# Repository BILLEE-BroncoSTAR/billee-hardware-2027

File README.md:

# BILLEE Hardware 2027
### By Luca Lanzillotta

This repository contains the hardware design and simulation files for the BILLEE Rover Control Module, schematic diagrams for the Science Control Module, F´/Zephyr firmware, Science Arduino firmware, and all supporting resources required to operate BILLEE for URC 2027.
If you are looking for our ROS2 Humble Software Stack, refer to [billee-software-2027](https://github.com/BroncoSpace-BILLEE/URC-2027).

## Table of contents

- [Rover architecture](#rover-architecture)
- [Repository layout](#repository-layout)
- [System architecture](#system-architecture)
- [BILLEE Rover Control Module PCB](#billee-rover-control-module-pcb)
  - [System overview](#system-overview)
  - [Power architecture](#power-architecture)
  - [Per-channel protection chain](#per-channel-protection-chain)
  - [Subsystems](#subsystems)
  - [Connectors](#connectors)
  - [RCM Firmware](#rcm-firmware)
- [BILLEE Science Control Module Schematic](#billee-science-control-module-schematic)
  - [SCM Firmware](#scm-firmware)
- [BILLEE Drivetrain Module Schematic](#billee-drivetrain-module-schematic)
- [BILLEE Arm Module Schematic](#billee-arm-module-schematic)
- [BILLEE Astronaut Module Schematic](#billee-astronaut-module-schematic)
- [Drivetrain motor calibration — ODESC Configuration](#drivetrain-motor-calibration--odesc-configuration)
- [Science spectrometer tooling](#science-spectrometer-tooling)
- [Astronaut video/audio streamer](#astronaut-videoaudio-streamer)
- [UV science camera](#uv-science-camera)
- [Getting started](#getting-started)
- [Design status](#design-status)
- [Contributors](#contributors)

## Rover architecture

A full-system view of BILLEE, from the operator at the ground station down to
each subsystem on the rover. Every link from the ground station to the rover
goes over the Ubiquiti Prism point-to-point link to the Jetson. The Jetson
then reaches the RCM and SCM over F´, the drivetrain over CAN, the arm over
GPIO, and the science instruments and astronaut module over USB, Bluetooth LE
and Wi-Fi. Thick arrows are power from the RCM, normal arrows are data, and the
dashed arrow is ROS2 control from the ground station.

```mermaid
flowchart TB
    %% ================= GROUND STATION =================
    OP(["Ground Station: Operator<br/>ROS2 control · F´ GDS · science + video dashboards"])

    %% ================= COMMS =================
    UBG["Ground Station Comms Link<br/>Ubiquiti Prism"]
    UBR["Rover Comms Link<br/>Ubiquiti Prism"]

    OP --> UBG
    UBG <-->|"point-to-point wireless link"| UBR

    %% ================= ROVER =================
    subgraph ROVER["BILLEE Rover"]
        direction TB

        JETSON["Jetson Orin AGX<br/>Main Compute · ROS2"]
        ZED["ZED 2 Camera"]
        RCM["Rover Control Module<br/>RP2350 · power distribution"]
        DRV["Drivetrain<br/>6× ODESC + NEO motors"]
        ARM["Arm Module<br/>3-axis arm + end effector"]

        subgraph SCI["Science"]
            direction TB
            SCM["Science Control Module<br/>Teensy 4.1"]
            SPEC["Spectroscopy<br/>Vernier spectrometer"]
            UV["UV Spectroscopy<br/>+ UV camera"]
            DRILL["Drill<br/>Regolith Extraction"]
            CHEM["Chemical Management<br/>pumps"]
            CACHE["Sample Cache<br/>+ Rotation"]
            SCM --> DRILL
            SCM --> CHEM
            SCM --> CACHE
            SCM --> UV
        end

        UBR -- "Ethernet" --> JETSON
        ZED -- "USB" --> JETSON
        JETSON <-->|"F´"| RCM
        JETSON <-->|"F´"| SCM
        JETSON -- "Bluetooth" --> SPEC
        JETSON -- "USB" --> UV
        JETSON -- "CAN" --> DRV
        JETSON -- "commands" --> ARM

        RCM == "power" ==> JETSON
        RCM == "power" ==> DRV
        RCM == "power" ==> ARM
        RCM == "power" ==> SCM
    end

    ASTRO["Astronaut Module<br/>Raspberry Pi 4B · camera + headset"]
    ASTRO -- "Wi-Fi video + audio" --> JETSON

    %% ================= ROS2 CONTROL =================
    OP -. "ROS2 control" .-> JETSON

    %% ================= STYLES =================
    classDef ground fill:#1f4e79,stroke:#0d2a45,color:#fff
    classDef comms fill:#7b3fa0,stroke:#4a2063,color:#fff
    classDef compute fill:#2e7d32,stroke:#1b4d1f,color:#fff
    classDef rcm fill:#c62828,stroke:#7f1414,color:#fff
    classDef science fill:#ef6c00,stroke:#8a3e00,color:#fff
    classDef motion fill:#455a64,stroke:#263238,color:#fff
    classDef astro fill:#00838f,stroke:#004f56,color:#fff

    class OP ground
    class UBG,UBR comms
    class JETSON,ZED compute
    class RCM rcm
    class SCM,SPEC,UV,DRILL,CHEM,CACHE science
    class DRV,ARM motion
    class ASTRO astro
```

The [System architecture](#system-architecture) section below zooms in on
the boards in this repo and how they connect.

## Repository layout

```
billee-hardware-2027/
├── BILLEE_Arm_Module/                    # KiCad project for the Arm Schematic
├── BILLEE_Astronaut_Module/              # KiCad project for the Astronaut Module Schematic
│   └── AstronautModuleAssembly/          # SolidWorks assembly: Raspberry Pi 4 mount + lid, Pi 4 datasheet
├── BILLEE_Drivetrain_Module/             # KiCad schematic documenting the drivetrain wiring (ODESC + NEO + CAN)
├── BILLEE_Rover_Control_Module_V1/       # KiCad project for the Rover Control Module
├── BILLEE_Science_Control_Module_V1/     # KiCad project for the Science Control Module
├── BILLEE-odesc-config-tool/             # Python tool: USB ODESC motor calibration
├── RunScienceSpectrometer/               # Offline Vernier spectrometer PWA + kiosk setup for the Jetson
├── astronaut-streamer/                   # Pi camera → Jetson → ground-station video + audio stream (git submodule)
├── fprime-billee-rcm/                    # F´ firmware for the RCM board (git submodule)
├── fprime-arduino-billee-scm/            # F´ firmware for the Science Control Module (git submodule)
├── uv_scienceCam/                        # USB Arducam → browser stream with live image tuning + snapshots (git submodule)
└── Makefile                              # Workspace bootstrap (`make setup`/`make rover`) + science/astronaut installers
```

## System architecture

BILLEE's compute and control hardware breaks down into a Jetson Orin AGX main
compute module, the Rover Control Module (RCM, this repo's primary board),
the Science Control Module (SCM), and the drivetrain's ODESC motor
controllers. The RCM both powers the Jetson and exchanges F´ telemetry/
commands with it; the SCM and the Jetson each run their own F´ deployment,
talking over separate USB connections and separate GDS dashboard ports so
both can be open at once.

```mermaid
flowchart TB
    Jetson["Jetson Orin AGX<br/>Main compute<br/>(ROS2 stack — billee-software-2027)"]

    subgraph RCM["Rover Control Module — BILLEE_Rover_Control_Module_V1 (KiCad)"]
        RCM_FW["RP2350<br/>fprime-billee-rcm (F´ / Zephyr)"]
    end

    subgraph SCM["Science Control Module — BILLEE_Science_Control_Module_V1 (KiCad)"]
        SCM_FW["Teensy 4.1<br/>fprime-arduino-billee-scm (F´)"]
    end

    RCM_FW -- "+20V power (CN2)" --> Jetson
    Jetson -- "USB CDC / F´ GDS :5000" --> RCM_FW
    Jetson -- "USB CDC / F´ GDS :5001" --> SCM_FW
    Jetson -- "Bluetooth LE" --> SPEC["Vernier Go Direct spectrometer<br/>(RunScienceSpectrometer)"]

    subgraph DRV["Drivetrain Module — BILLEE_Drivetrain_Module (KiCad)"]
        ODESC["6x ODESC V4.2 + NEO motors"]
    end

    RCM_FW -- "6x switched DRIVE outputs" --> ODESC
    Jetson -- "USB CANable / CAN bus" --> ODESC
    subgraph ARMM["Arm Module — BILLEE_Arm_Module (KiCad)"]
        ARM["3-axis arm actuators<br/>+ end-effector solenoid"]
    end

    RCM_FW -- "switched ARM output" --> ARM
    Jetson -- "GPIO27 → solenoid relay" --> ARM
    RCM_FW -- "switched SCIENCE output" --> SCM_FW

    ODESC -. "USB, one-time calibration" .-> TOOL["BILLEE-odesc-config-tool<br/>(odrive Python tool)"]
```

Solid arrows are runtime power/data paths; the dashed arrow is the ODESC
calibration tool's occasional USB connection, not part of the running
topology. Runtime drivetrain/arm motor commands come from the ROS2 stack in
[billee-software-2027](https://github.com/BroncoSpace-BILLEE/URC-2027), outside
this repo's scope — the RCM only switches and protects their power.

### Hardware ↔ Firmware

| Hardware (KiCad project) | Firmware | Target | Role |
|---|---|---|---|
| [`BILLEE_Rover_Control_Module_V1/`](BILLEE_Rover_Control_Module_V1/) | [`fprime-billee-rcm`](fprime-billee-rcm/README.md) | RP2350 (F´ / Zephyr) | Power distribution/gating for DRIVE, ARM, and SCIENCE; powers the Jetson; reports subsystem/E-Stop/thermal telemetry over USB |
| [`BILLEE_Science_Control_Module_V1/`](BILLEE_Science_Control_Module_V1/) — | [`fprime-arduino-billee-scm`](fprime-arduino-billee-scm/README.md) | Teensy 4.1 (F´) | Science instrument control, USB CDC to Jetson |
| [`BILLEE_Arm_Module/`](BILLEE_Arm_Module/) — arm wiring (off-the-shelf actuators, documented here) | — | — | Arm axis actuators and end-effector solenoid, powered from the RCM's switched ARM output |
| [`BILLEE_Drivetrain_Module/`](BILLEE_Drivetrain_Module/) — ODESC motor controllers (third-party hardware, wiring documented here) | [`BILLEE-odesc-config-tool`](BILLEE-odesc-config-tool/README.md) | ODrive-based ODESC | One-time/occasional USB calibration tool (encoder/motor cal, CAN node ID) — not runtime firmware |

BILLEE is a Mars-rover-style rover platform built as a university project. This repository holds the hardware for the **Rover Control Module (RCM)** — the rover's central power distribution and control board. It takes in power from up to four independent battery packs, gates and protects eight switched high-current outputs (six drivetrain channels plus dedicated ARM and SCIENCE subsystem outputs), and hosts the RP2350 microcontroller that supervises the whole board, running [NASA JPL's F´ (F Prime)](https://fprime.jpl.nasa.gov/) flight software framework on Zephyr RTOS.

## BILLEE Rover Control Module PCB

## System overview

```mermaid
flowchart TB
    subgraph Power["Power inputs (4 independent battery packs)"]
        LOGIC_BATT["LOGIC BATT<br/>22.2V / 6S<br/>CN1"]
        DRIVE_BATT["DRIVE BATT<br/>14.4V / 4S<br/>CN7"]
        ARM_BATT["ARM BATT<br/>22.2V / 6S<br/>CN9"]
        SCI_BATT["SCIENCE BATT<br/>22.2V / 6S<br/>CN8"]
    end

    subgraph Control["Control plane"]
        RP2350["RP2350<br/>Fprime-zephyr"]
        ESTOP["E-Stop circuit"]
        FLASH["W25Q128 flash"]
        TEMP["MCP9808 temp sensors"]
        RP2350 --- FLASH
        RP2350 --- TEMP
        ESTOP -- "cuts ARM / SCIENCE / DRIVE enables" --> RP2350
    end

    subgraph Outputs["Switched, gated, current-sensed outputs"]
        DRIVE_OUT["6x DRIVE channels<br/>XT60, CN10-CN15"]
        ARM_OUT["ARM output<br/>XT60 x2, CN17/CN18"]
        SCI_OUT["SCIENCE output<br/>XT60, CN16"]
    end

    subgraph Aux["Auxiliary rails"]
        LOGIC3V3["+3.3V RP2350 / logic"]
        LOGIC12V["+12V AUX (gate driver bias)"]
        POE["+22.2V POE out<br/>XT60, CN3"]
        JETSON["+20V Jetson out<br/>XT60, CN2"]
    end

    LOGIC_BATT --> Reg["Onboard regulation<br/>(buck converters + e-fuses)"]
    Reg --> LOGIC3V3
    Reg --> LOGIC12V
    Reg --> POE
    Reg --> JETSON
    Reg -. powers control plane .-> RP2350

    DRIVE_BATT --> DRIVE_OUT
    ARM_BATT --> ARM_OUT
    SCI_BATT --> SCI_OUT

    RP2350 -- "GPIO enable per channel" --> DRIVE_OUT
    RP2350 -- "GPIO enable" --> ARM_OUT
    RP2350 -- "GPIO enable" --> SCI_OUT
```

## Power architecture

Every high-current output is switched, not just fused — each channel has its own MOSFET high-side switch, gate driver, and current/voltage sense IC, controlled by the RP2350 and independently protected against overvoltage.

| Input | Voltage | Pack | Connector | Feeds |
|---|---|---|---|---|
| LOGIC | 22.2V nominal | 6S | CN1 (XT90) | Onboard regulation → 3.3V logic, 12V gate-driver bias, POE out, Jetson out |
| DRIVE | 14.4V nominal | 4S | CN7 (XT90) | 6x independently gated drivetrain outputs |
| ARM | 22.2V nominal | 6S | CN9 (XT90) | ARM actuator output (dedicated, not shared with LOGIC) |
| SCIENCE | 22.2V nominal | 6S | CN8 (XT90) | SCIENCE payload output (dedicated, not shared with LOGIC) |

ARM and SCIENCE each have their own battery input rather than sharing the LOGIC bus — this keeps their (higher-current, motor-driven) load switching electrically isolated from the board's own logic supply.

## Per-channel protection chain

The same signal chain protects all eight switched outputs (six DRIVE channels, ARM, SCIENCE) — this is what sits between the RP2350's enable GPIO and the actual output connector:

```mermaid
flowchart LR
    GPIO["RP2350 GPIO<br/>(per-channel enable)"] --> BUF["Logic buffer<br/>(SN74LVC08A AND gate)"]
    ESTOP["E-Stop status"] --> BUF
    BUF --> DRV["LTC7001<br/>gate driver"]
    OVLO["OVLO divider<br/>(866k/34k → 1.21V trip)"] --> DRV
    DRV --> FET["IPT007N06N<br/>high-side MOSFET<br/>(60V rated)"]
    FET --> ISENSE["INA780x<br/>current + voltage sense<br/>(85V CMV)"]
    ISENSE --> OUT["Output connector"]
```

Each channel's overvoltage lockout trips at roughly the same ~32V threshold regardless of that channel's nominal rail — set by a fixed 866kΩ/34kΩ divider into the gate driver's 1.21V comparator reference. The MOSFETs and current-sense amplifiers were selected with wide margin above every rail on this board (60V and 85V ratings against a top end around 25V), so the same switch/sense stage is reused across the 14.4V DRIVE channels and the 22.2V ARM/SCIENCE channels without modification.

## Subsystems

| Subsystem | Sheet | What's there |
|---|---|---|
| RP2350A | `mcurp2350.kicad_sch` | RP2350 MCU, crystal, QSPI flash, USB-C, SWD debug header, GPIO breakout |
| Logic Subsystem | `power.kicad_sch` | Buck regulators, e-fuses, logic/auxiliary rail generation |
| Subsystem Power Control | `estop.kicad_sch` | E-stop circuit, all 8 gate-driver/switch/sense channels, OVLO dividers |

## Connectors

| Ref | Part | Count | Purpose |
|---|---|---|---|
| CN1 | XT90PW | 1 | LOGIC battery input (22.2V) |
| CN7 | XT90PW | 1 | DRIVE battery input (14.4V) |
| CN8 | XT90PW | 1 | SCIENCE battery input (22.2V) |
| CN9 | XT90PW | 1 | ARM battery input (22.2V) |
| CN10–CN15 | XT60PW | 6 | DRIVE channel outputs 1–6 |
| CN16 | XT60PW | 1 | SCIENCE output |
| CN17, CN18 | XT60PW | 2 | ARM output |
| CN2 | XT60PW | 1 | Jetson power output (+20V) |
| CN3 | XT60PW | 1 | POE output (+22.2V) |
| CN4, CN5 | XT60PW | 2 | Auxiliary +12V outputs |
| CN6 | DF11-18DP | 1 | RP2350 GPIO breakout (9 GPIO + ADC0/1 + power/GND) |
| USB1 | USB-C | 1 | RP2350 USB |
| J1 | 2.54mm header | 1 | SWD debug (SWCLK/SWD/GND) |

## RCM Firmware

The RCM's RP2350 runs [F´](https://fprime.jpl.nasa.gov/) on Zephyr RTOS —
subsystem power enable/disable, E-Stop handling, and MCP9808/INA780B thermal
and power telemetry, communicating with the Jetson over USB CDC. To get
started:

```bash
cd fprime-billee-rcm
make setup      # creates fprime-venv, inits submodules, installs requirements.txt
```

See [`fprime-billee-rcm/README.md`](fprime-billee-rcm/README.md) for the rest
(`make setup-zephyr`, `make build-rp2350`, flashing, GDS), and
[`docs/OPERATOR_MANUAL.md`](fprime-billee-rcm/docs/OPERATOR_MANUAL.md) for the
command/telemetry reference.

## BILLEE Science Control Module Schematic

[`BILLEE_Science_Control_Module_V1/`](BILLEE_Science_Control_Module_V1/)
is an early-stage KiCad project; this section will be filled in with the
schematic and hardware documentation once the module design is integrated.

## SCM Firmware

The SCM runs F´ on a Teensy 4.1, communicating with the Jetson over its own
USB CDC connection (GDS on port 5001, alongside the RCM's on port 5000). To
get started:

```bash
cd fprime-arduino-billee-scm
make setup      # creates fprime-venv, inits submodules, installs Python deps
```

See [`fprime-arduino-billee-scm/README.md`](fprime-arduino-billee-scm/README.md)
for the rest (`make setup-arduino`, `make generate`, `make build`, flashing).

## BILLEE Drivetrain Module Schematic

[`BILLEE_Drivetrain_Module/`](BILLEE_Drivetrain_Module/) is a KiCad
schematic documenting the drivetrain wiring as built for the '24 URC season:
six ODESC V4.2 controllers, each driving a NEO brushless motor with Hall
feedback, fed from the RCM's six switched `DRIVE` outputs and sharing a CAN
bus that reaches the Jetson through a USB CANable. It's wiring documentation
for the third-party hardware, not a custom PCB.

## BILLEE Arm Module Schematic

[`BILLEE_Arm_Module/`](BILLEE_Arm_Module/) is a KiCad schematic documenting
the 2027 robotic arm's wiring: P17/P20 harmonic-reducer actuators on the 1st,
2nd and 3rd axes, Yellow Jacket motors, and a GX20 14-pin bulkhead connector
between the rover body and the arm. The end effector carries a typing
solenoid, switched by a logic-level relay driven from Jetson GPIO27
(header pin 15). Power comes from the RCM's `+22.2V_ARM` output through a
front-panel Anderson Powerpole. Electronics by Luca Lanzillotta and Jason
Lau; mechanical design by Justin Chang.

## BILLEE Astronaut Module Schematic

[`BILLEE_Astronaut_Module/`](BILLEE_Astronaut_Module/) is a KiCad
block-diagram schematic of the astronaut module's hardware: a Raspberry Pi 4B
powered over USB-C to USB-C from an Anker Prime 27,650 mAh power bank, with
wired headphones on a 3.5 mm jack (no mic). This is the Pi that runs the
sender side of the [astronaut video/audio streamer](#astronaut-videoaudio-streamer).
Like the drivetrain schematic, it documents off-the-shelf hardware and is not
a custom PCB.

[`AstronautModuleAssembly/`](BILLEE_Astronaut_Module/AstronautModuleAssembly/)
holds the SolidWorks models for the module's enclosure:
`AstronautModuleAssembly.SLDASM`, the `PiMount` and `PiMountLid` parts, and
the Raspberry Pi 4 datasheet for reference.

## Drivetrain motor calibration — ODESC Configuration

[`BILLEE-odesc-config-tool`](BILLEE-odesc-config-tool/README.md) is a
Python tool (not firmware) for calibrating an ODESC-controlled drivetrain
motor over USB — encoder/motor calibration, CAN node ID setup, and saving
config to flash. It's a one-time/occasional setup step per motor, separate
from runtime motor control.

## Science spectrometer tooling

[`RunScienceSpectrometer`](RunScienceSpectrometer/README.md) sets up an
offline-capable copy of Vernier's Spectral Analysis PWA on the Jetson, talking
to a Go Direct spectrometer over Bluetooth LE, with an optional headless
VNC kiosk mode.

## Astronaut video/audio streamer

[`astronaut-streamer`](https://github.com/LucaLanzi/astronaut-streamer) (git
submodule) streams live video and audio from a USB camera on a Raspberry Pi 4B
to the Jetson over the Jetson's Wi-Fi hotspot. The Jetson forwards it to a
browser at the ground station over the Ubiquiti Prism link, at
`https://10.110.0.230:8443`, and the ground station can talk back to the
astronaut's headphones. Everything installs from this repo's root:

```bash
make astronaut jetson   # on the Jetson: packages, media server, dashboard, services, hotspot
make astronaut pi       # on the Pi: packages, Wi-Fi, SSH, sender service
make astronaut probe    # on the Pi: bench check (camera, mic, speaker, encoders, Wi-Fi)
make astronaut status   # on either: what's running
make astronaut jetson ip rover 192.168.4.97/22   # other addresses (defaults: the rover's)
make astronaut          # every command (logs, restart, test-pattern, view, test, e2e, ...)
```

Step by step: [`astronaut-streamer/docs/RUN_GUIDE.md`](astronaut-streamer/docs/RUN_GUIDE.md).
Full reference: [`astronaut-streamer/docs/SETUP.md`](astronaut-streamer/docs/SETUP.md).
Hardware test plan:
[`astronaut-streamer/docs/TEST_CHECKLIST.md`](astronaut-streamer/docs/TEST_CHECKLIST.md).
Design: [`astronaut-streamer/PLAN.md`](astronaut-streamer/PLAN.md).

## UV science camera

[`uv_scienceCam`](https://github.com/LucaLanzi/uv_scienceCam) (git
submodule) streams a USB (UVC) Arducam to a browser over the network. From
the browser you can tune the camera's image controls live (exposure, gain,
white balance, etc.), save/load tuning profiles as JSON, and take a
full-resolution picture that downloads to the viewing computer. It serves on
port 8090 to stay clear of the ports already in use on the Jetson. On the
machine the camera is plugged into:

```bash
cd uv_scienceCam
make setup      # apt packages, .venv, video group, firewall port
make list       # find the camera
make run        # camera 0, largest MJPG size, port 8090
```

Then open `http://<camera-host-ip>:8090/`. See
[`uv_scienceCam/README.md`](uv_scienceCam/README.md) for options and the HTTP
API.

## Getting started

1. Clone with submodules — the F´ component library is a separate repo:
   ```
   git clone --recurse-submodules https://github.com/BroncoSpace-BILLEE/billee-hardware-2027.git
   ```
   Already cloned, or need to resync after a branch change? Run `make rover` from
   the repo root — it checks out `lucadev`, pulls, and updates every submodule
   recursively. `make help` lists all targets.
2. Open `BILLEE_Rover_Control_Module_V1/BILLEE_Rover_Control_Module_V1.kicad_pro` in KiCad. The custom library footprints under `lib/` are wired up via the project's `fp-lib-table`/`sym-lib-table` — no extra setup needed.
3. To order the board: everything JLCPCB needs is pre-generated in `BILLEE_Rover_Control_Module_V1/jlcpcb/production_files/` — `BOM-*.csv`, `CPL-*.csv`, and `GERBER-*.zip`. If you change the design, regenerate these (via the KiCad JLCPCB/Fabrication-Toolkit plugin) before ordering — the production files are a separate export step from the schematic/PCB and don't update automatically.
4. Firmware for the RCM runs [F´](https://fprime.jpl.nasa.gov/) on Zephyr; the board-specific F´ components live in the `fprime-billee-rcm` submodule.
5. To calibrate a drivetrain motor's ODESC, see [`BILLEE-odesc-config-tool/README.md`](BILLEE-odesc-config-tool/README.md).
6. To set up the science spectrometer on the Jetson, run `make science` from the repo root, or see [`RunScienceSpectrometer/README.md`](RunScienceSpectrometer/README.md).
7. To set up the astronaut video/audio stream, run `make astronaut jetson` on the Jetson and `make astronaut pi` on the Pi, or see [`astronaut-streamer/docs/SETUP.md`](astronaut-streamer/docs/SETUP.md).
8. To stream the UV science camera, run `make setup` then `make run` inside `uv_scienceCam/`, or see [`uv_scienceCam/README.md`](uv_scienceCam/README.md).

## Design status

This board has been ordered and works almost perfectly. There are two open issues in this git repo that highlight two outstanding issues. Fortunately the two design flaws are minimal and do not affect the functionality of the board.

## Contributors

- Luca Lanzi ([@LucaLanzi](https://github.com/LucaLanzi))
- Jason Suarez ([@Plush-Jason](https://github.com/Plush-Jason))

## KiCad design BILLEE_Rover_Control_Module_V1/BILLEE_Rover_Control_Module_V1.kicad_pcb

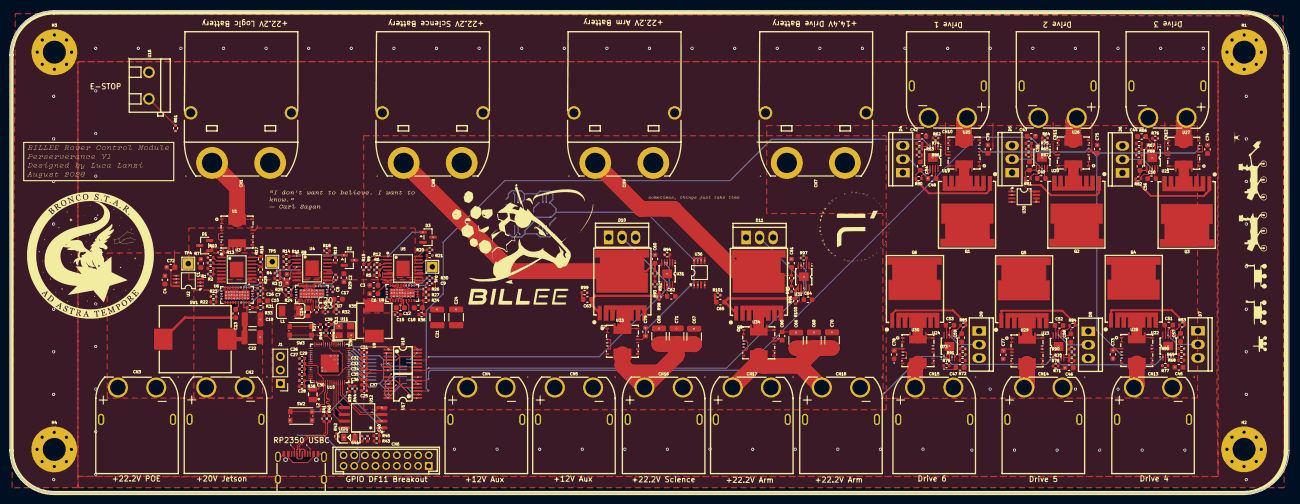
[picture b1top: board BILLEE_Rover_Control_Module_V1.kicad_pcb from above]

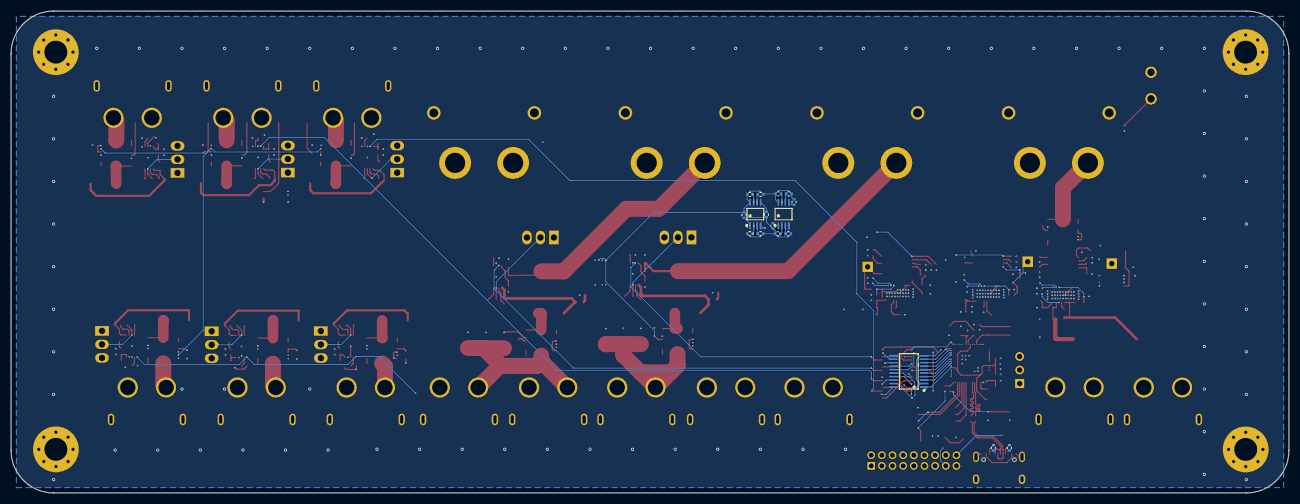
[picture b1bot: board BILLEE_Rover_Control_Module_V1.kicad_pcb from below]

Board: 4 copper layers, 240.0 x 90.5 mm, 269 parts (17 on the bottom side), 219 nets.

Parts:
C1, C2, C3: 220n; C_0603_1608Metric
C4, C5, C6, C48, C49, C50, C51, C52, C53, C62, C64: 4.7u; C_0603_1608Metric
C7, C10, C11, C12: 1u; C_0402_1005Metric
C8, C9: 10n; C_0402_1005Metric
C13, C14, C15, C72, C73, C74, C75, C76, C77, C78, C79, C80: 0.1u; C_0603_1608Metric
C16, C18: 10p; C_0603_1608Metric
C17: 4.7p; C_0603_1608Metric
C19, C21, C22, C24, C66, C67, C68, C69, C70, C71: 10u; C_1210_3225Metric
C20, C23: 22u; C_0402_1005Metric
C25, C26, C28, C29: 4.7u; C_0402_1005Metric
C27, C30, C31, C32, C33, C34, C35, C36, C37, C40: 100n; C_0402_1005Metric
C38, C39: 15p; C_0402_1005Metric
C41: 0.1u; C_0402_1005Metric
C42, C43, C44, C45, C46, C47, C60, C61: 10u; C_0603_1608Metric
C54, C55, C56, C57, C58, C59, C63, C65: 0.47u; C_0603_1608Metric
CN1, CN7, CN8, CN9: XT90PW-M.G.Y; CONN-TH_XT90PW-M.G.Y
CN2, CN3, CN4, CN5, CN10, CN11, CN12, CN13, CN14, CN15, CN16, CN17, CN18: XT60PW-M; CONN-TH_XT60PW-M
CN6: DF11-18DP-2DSA; CONN-TH_18P-P2.00_HCTL_HC-PHD-2X9A
D1, D2, D3: BAS21; SOT-23
D4, D5, D6, D7, D8, D9, D10, D11: MBR30200CT; TO-220-3_L10.0-W4.5-P2.54-L-1
H1, H2, H3, H4: MountingHole_Pad; MountingHole_4.3mm_M4_Pad_Via
J1: 2.54mm Header; PinHeader_1x03_P2.54mm_Vertical
L1: 8.2u; L1210
L2: 3.3u; IND-SMD_L2.0-W1.6_AOTA-B201610S3R3-101-T
LED1: FC-2012UGK-520D5; LED0805-R-RD
Q1, Q2, Q3, Q4, Q5, Q6, Q7, Q8: IPT007N06N; HSOF-8_IPT007N06N
R1, R3, R5: 33K; R_0402_1005Metric
R2, R4, R6: 10K; R_0402_1005Metric
R7, R8, R9, R39, R46: 1k; R_0402_1005Metric
R10, R11, R12, R16, R17, R18, R19, R20, R21: 15k; R_0402_1005Metric
R13, R14, R15: 4.7k; R_0402_1005Metric
R22, R24, R26, R80, R81, R82, R83, R84, R85, R98, R100: 200k; R_0402_1005Metric
R23, R25, R27, R31, R37, R45, R47, R48, R49, R50, R51, R52, R53, R54, R55, R56, R59, R60, R61: 10k; R_0402_1005Metric
R28, R29: 110k; R_0402_1005Metric
R30: 41.2K; R_0402_1005Metric
R32: 412k; R_0402_1005Metric
R33: 196k; R_0402_1005Metric
R34: 88.7K; R_0402_1005Metric
R35, R36: 1M; R_0402_1005Metric
R38: 33; R_0402_1005Metric
R40, R41: 27; R_0402_1005Metric
R42: 330; R_0402_1005Metric
R43: DNF; R_0402_1005Metric
R44: 0; R_0402_1005Metric
R57, R58: 5.1k; R_0402_1005Metric
R62, R64, R66, R68, R70, R72, R92, R95: 866k; R_0402_1005Metric
R63, R65, R67, R69, R71, R73, R93, R96: 34k; R_0402_1005Metric
R74, R75, R76, R77, R78, R79, R94, R97: 150k; R_0402_1005Metric
R86, R87, R88, R89, R90, R91, R99, R101: 10; R_0402_1005Metric
SW1: 33uH; IND-SMD_L13.5-W12.6
SW2: KMR2; SW_Push_1P1T_NO_CK_KMR2
SW3: RESET SW; SW_Push_1P1T_NO_CK_KMR2
TP4, TP5, TP6: TestPoint; TestPoint_THTPad_2.0x2.0mm_Drill1.0mm
U1, U25, U26, U27, U28, U29, U30, U33, U34: INA780BIDEKR; VQFN-15_L6.0-W6.0-P0.60-TL
U2, U35, U36: MCP9808T-E/MS; MSOP-8_L3.0-W3.0-P0.65-LS4.9-BL
U3, U4, U5: TPS1HA08BQPWPRQ1; HTSSOP-16_L5.0-W4.4-P0.65-LS6.4-TL-EP2.9
U6, U7, U8: LT8612EUDE#TRPBF; QFN-28_L6.0-W3.0-P0.50-BL-EP
U9: 10uH; IND-SMD_L7.2-W6.6_GPSR07X0
U10: RP2350A_C42411118; QFN-60_L7.0-W7.0-P0.40-TL-EP3.4
U11: ABM8-272-T3_C20625731; CRYSTAL-SMD_4P-L3.2-W2.5-BL
U12: W25Q128JVSIQTR; SOIC-8_L5.3-W5.3-P1.27-LS8.0-BL
U13, U14: TCA4307DGKR; VSSOP-8_L3.0-W3.0-P0.65-LS4.9-BL
U15: TXS0108EPWR; TSSOP-20_L6.5-W4.4-P0.65-LS6.4-BL
U16: ESTOP; CONN-TH_P5.00_KF301-5.0-2P
U17, U18: SN74LVC08APWR; TSSOP-14_L5.0-W4.4-P0.65-LS6.4-BL
U19, U20, U21, U22, U23, U24, U31, U32: LTC7001IMSE#PBF; MSOP-10_L3.0-W3.0-P0.50-LS4.9-BL-EP
USB1: TYPE-C 16PIN 2MD; USB-C-SMD_TYPE-C-16PIN-2MD-073

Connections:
+1V1: C26.1, C27.1, C29.1, C30.1, L2.2, U10.6 (DVDD), U10.23 (DVDD), U10.39 (DVDD), U10.50 (VREG_FB)
+3.3V_RP2350_VCC: C17.1, C20.1, C23.1, C25.1, C31.1, C32.1, C33.1, C34.1, C35.1, C36.1, C37.1, C40.1, C41.2, C72.2, C73.2, C74.2, C75.2, C76.2, C77.2, C78.2, C79.2, C80.2, CN6.11, CN6.12, L1.2, R35.1, R38.1, R42.1, R45.1, R47.2, R48.2, R49.2, R50.2, R51.2, R52.2, R53.2, R54.2, R55.2, R56.2, R59.2, R60.2, U1.12 (VS), U2.8 (VDD), U7.22 (BIAS), U10.1 (IOVDD), U10.11 (IOVDD), U10.20 (IOVDD), U10.30 (IOVDD), U10.38 (IOVDD), U10.44 (ADC_AVDD), U10.45 (IOVDD), U10.49 (VREG_VIN), U10.53 (USB_OTP_VDD), U10.54 (QSPI_IOVDD), U12.8 (VCC), U13.8 (VCC), U14.8 (VCC), U15.2 (VCCA), U15.10 (OE), U15.19 (VCCB), U16.1, U17.14 (VCC), U18.14 (VCC), U25.12 (VS), U26.4 (A0), U26.12 (VS), U27.12 (VS), U28.3 (A1), U28.12 (VS), U29.3 (A1), U29.4 (A0), U29.12 (VS), U30.3 (A1), U30.12 (VS), U33.4 (A0), U33.12 (VS), U34.12 (VS), U35.7 (A0), U35.8 (VDD), U36.6 (A1), U36.8 (VDD)
+12V_AUX_VCC: C18.1, C21.1, C24.1, CN4.2 (+), CN5.2 (+), R36.1, U8.22 (BIAS), U9.2, U19.1 (VCC), U20.1 (VCC), U21.1 (VCC), U22.1 (VCC), U23.1 (VCC), U24.1 (VCC), U31.1 (VCC), U32.1 (VCC)
+14.4V_DRIVE1: Q1.2 (S), U25.14 (VBUS), U25.15 (IS+)
+14.4V_DRIVE1_SENSOR_OUT: CN10.2 (+), U25.8 (IS–)
+14.4V_DRIVE2: Q2.2 (S), U26.14 (VBUS), U26.15 (IS+)
+14.4V_DRIVE2_SENSOR_OUT: CN11.2 (+), U26.8 (IS–)
+14.4V_DRIVE3: Q3.2 (S), U27.14 (VBUS), U27.15 (IS+)
+14.4V_DRIVE3_SENSOR_OUT: CN12.2 (+), U27.8 (IS–)
+14.4V_DRIVE4: Q4.2 (S), U28.14 (VBUS), U28.15 (IS+)
+14.4V_DRIVE4_SENSOR_OUT: CN13.2 (+), U28.8 (IS–)
+14.4V_DRIVE5: Q5.2 (S), U29.14 (VBUS), U29.15 (IS+)
+14.4V_DRIVE5_SENSOR_OUT: CN14.2 (+), U29.8 (IS–)
+14.4V_DRIVE6: Q6.2 (S), U30.14 (VBUS), U30.15 (IS+)
+14.4V_DRIVE6_SENSOR_OUT: CN15.2 (+), U30.8 (IS–)
+14.4V_DRIVE_BATT: C42.1, C43.1, C44.1, C45.1, C46.1, C47.1, CN7.1 (+), Q1.3 (D), Q2.3 (D), Q3.3 (D), Q4.3 (D), Q5.3 (D), Q6.3 (D), R62.2, R64.2, R66.2, R68.2, R70.2, R72.2
+20V_JETSON_VCC: C16.1, C19.1, C22.1, CN2.2 (+), R33.1, SW1.2, U6.22 (BIAS)
+22.2V_ARM: Q8.2 (S), U34.14 (VBUS), U34.15 (IS+)
+22.2V_ARM_BATT: C61.1, CN9.1 (+), Q8.3 (D), R95.2
+22.2V_ARM_SENSOR_OUT: C66.1, C68.1, C70.1, CN17.2 (+), CN18.2 (+), U34.8 (IS–)
+22.2V_LOGIC: CN1.1 (+), U1.14 (VBUS), U1.15 (IS+)
+22.2V_LOGIC_POWER_SENSOR_OUT: C1.1, C2.1, C3.1, R1.1, R3.1, R5.1, U1.8 (IS–), U3.17 (VBB), U4.17 (VBB), U5.17 (VBB)
+22.2V_POE_VCC: C4.1, CN3.2 (+), R22.2, TP4.1 (1_1), U3.6 (VOUT), U6.5 (VIN)
+22.2V_SCIENCE: Q7.2 (S), U33.14 (VBUS), U33.15 (IS+)
+22.2V_SCIENCE_BATT: C60.1, CN8.1 (+), Q7.3 (D), R92.2
+22.2V_SCIENCE_SENSOR_OUT: C67.1, C69.1, C71.1, CN16.2 (+), U33.8 (IS–)
/RP2350A/DP_D+: R40.1, U10.52 (USB_DP)
/RP2350A/DP_D-: R41.1, U10.51 (USB_DM)
/RP2350A/FLASH_SS: R43.2, R44.2, R45.2, U12.1 (~CS)
/RP2350A/GPIO13: CN6.1, U10.17 (GPIO13)
/RP2350A/GPIO14: CN6.2, U10.18 (GPIO14)
/RP2350A/GPIO15: CN6.3, U10.19 (GPIO15)
/RP2350A/GPIO16: CN6.4, U10.27 (GPIO16)
/RP2350A/GPIO17: CN6.5, U10.28 (GPIO17)
/RP2350A/GPIO18: CN6.6, U10.29 (GPIO18)
/RP2350A/GPIO19: CN6.7, U10.31 (GPIO19)
/RP2350A/GPIO20: CN6.8, U10.32 (GPIO20)
/RP2350A/GPIO21: CN6.9, U10.33 (GPIO21)
/RP2350A/GPIO22: CN6.18, U10.34 (GPIO22)
/RP2350A/GPIO23: CN6.17, U10.35 (GPIO23)
/RP2350A/GPIO24: CN6.16, U10.36 (GPIO24)
/RP2350A/GPIO25: CN6.15, U10.37 (GPIO25)
/RP2350A/GPIO26_ADC0: CN6.14, U10.40 (GPIO26_ADC0)
/RP2350A/GPIO27_ADC1: CN6.13, U10.41 (GPIO27_ADC1)
/RP2350A/QSPI_SCLK: U10.56 (QSPI_SCLK), U12.6 (CLK)
/RP2350A/QSPI_SD0: U10.57 (QSPI_SD0), U12.5 (DI(IO0))
/RP2350A/QSPI_SD1: U10.59 (QSPI_SD1), U12.2 (DO(IO1))
/RP2350A/QSPI_SD2: U10.58 (QSPI_SD2), U12.3 (IO2)
/RP2350A/QSPI_SD3: U10.55 (QSPI_SD3), U12.7 (IO3)
/RP2350A/QSPI_SS: R39.2, R44.1, U10.60 (QSPI_SS)
/RP2350A/RUN: SW3.2, U10.26 (RUN)
/RP2350A/SWCLK: J1.2, U10.24 (SWCLK)
/RP2350A/SWD: J1.3, U10.25 (SWD)
/RP2350A/SW_RUN_R: R37.2, SW3.1
/RP2350A/VREG_LX: L2.1, U10.48 (VREG_LX)
/RP2350A/XIN: C38.2, U10.21 (XIN), U11.1
/RP2350A/XOUT: R46.2, U10.22 (XOUT)
/RP2350A/XOUT_R: C39.2, R46.1, U11.3
/RP2350A/~USB_BOOT: R39.1, SW2.2
/Subsystem Power Control/GATE_ARM: U18.8 (3Y), U32.4 (INP)
/Subsystem Power Control/GATE_DRIVE1: U17.3 (1Y), U19.4 (INP)
/Subsystem Power Control/GATE_DRIVE2: U17.6 (2Y), U20.4 (INP)
/Subsystem Power Control/GATE_DRIVE3: U17.8 (3Y), U21.4 (INP)
/Subsystem Power Control/GATE_DRIVE4: U17.11 (4Y), U22.4 (INP)
/Subsystem Power Control/GATE_DRIVE5: U18.3 (1Y), U23.4 (INP)
/Subsystem Power Control/GATE_DRIVE6: U18.6 (2Y), U24.4 (INP)
/Subsystem Power Control/GATE_SCIENCE: U18.11 (4Y), U31.4 (INP)
BUFF_ARM_EN: U15.13 (B7), U18.10 (3B)
BUFF_DRIVE_EN_1: U15.20 (B1), U17.2 (1B)
BUFF_DRIVE_EN_2: U15.18 (B2), U17.5 (2B)
BUFF_DRIVE_EN_3: U15.17 (B3), U17.10 (3B)
BUFF_DRIVE_EN_4: U15.16 (B4), U17.13 (4B)
BUFF_DRIVE_EN_5: U15.15 (B5), U18.2 (1B)
BUFF_DRIVE_EN_6: U15.14 (B6), U18.5 (2B)
BUFF_E_STOP_STATUS: R61.2, U10.16 (GPIO12), U16.2, U17.1 (1A), U17.4 (2A), U17.9 (3A), U17.12 (4A), U18.1 (1A), U18.4 (2A), U18.9 (3A), U18.12 (4A)
BUFF_SCIENCE_EN: U15.12 (B8), U18.13 (4B)
BUFF_SCL_0: R53.1, U1.3 (A1), U1.4 (A0), U1.6 (SCL), U13.2 (SCLOUT), U25.6 (SCL), U26.6 (SCL), U27.4 (A0), U27.6 (SCL), U28.6 (SCL), U29.6 (SCL), U30.4 (A0), U30.6 (SCL), U33.3 (A1), U33.6 (SCL), U34.3 (A1), U34.6 (SCL)
BUFF_SCL_1: R54.1, U2.2 (SCL), U14.2 (SCLOUT), U35.2 (SCL), U36.2 (SCL)
BUFF_SDA_0: R55.1, U1.5 (SDA), U13.7 (SDAOUT), U25.5 (SDA), U26.5 (SDA), U27.5 (SDA), U28.5 (SDA), U29.5 (SDA), U30.5 (SDA), U33.5 (SDA), U34.5 (SDA)
BUFF_SDA_1: R56.1, U2.1 (SDA), U14.7 (SDAOUT), U35.1 (SDA), U36.1 (SDA)
GND: C1.2, C2.2, C3.2, C4.2, C5.2, C6.2, C7.2, C8.2, C9.2, C10.2, C11.2, C12.2, C19.2, C20.2, C21.2, C22.2, C23.2, C24.2, C25.2, C26.2, C27.2, C28.2, C29.2, C30.2, C31.2, C32.2, C33.2, C34.2, C35.2, C36.2, C37.2, C38.1, C39.1, C40.2, C41.1, C42.2, C43.2, C44.2, C45.2, C46.2, C47.2, C60.2, C61.2, C66.2, C67.2, C68.2, C69.2, C70.2, C71.2, C72.1, C73.1, C74.1, C75.1, C76.1, C77.1, C78.1, C79.1, C80.1, CN1.2 (-), CN1.3, CN1.4, CN2.1 (-), CN2.3, CN2.4, CN3.1 (-), CN3.3, CN3.4, CN4.1 (-), CN4.3, CN4.4, CN5.1 (-), CN5.3, CN5.4, CN6.10, CN7.2 (-), CN7.3, CN7.4, CN8.2 (-), CN8.3, CN8.4, CN9.2 (-), CN9.3, CN9.4, CN10.1 (-), CN10.3, CN10.4, CN11.1 (-), CN11.3, CN11.4, CN12.1 (-), CN12.3, CN12.4, CN13.1 (-), CN13.3, CN13.4, CN14.1 (-), CN14.3, CN14.4, CN15.1 (-), CN15.3, CN15.4, CN16.1 (-), CN16.3, CN16.4, CN17.1 (-), CN17.3, CN17.4, CN18.1 (-), CN18.3, CN18.4, D1.3 (K), D2.3 (K), D3.3 (K), D4.1, D4.3, D5.1, D5.3, D6.1, D6.3, D7.1, D7.3, D8.1, D8.3, D9.1, D9.3, D10.1, D10.3, D11.1, D11.3, H1.1 (1_1), H2.1 (1_1), H3.1 (1_1), H4.1 (1_1), J1.1, LED1.2 (K), R2.2, R4.2, R6.2, R7.2, R8.2, R9.2, R10.2, R11.2, R12.2, R13.1, R14.1, R15.1, R16.2, R17.2, R18.2, R19.2, R20.2, R21.2, R23.1, R25.1, R27.1, R28.1, R29.1, R30.1, R31.2, R32.2, R34.2, R37.1, R57.2, R58.2, R61.1, R63.1, R65.1, R67.1, R69.1, R71.1, R73.1, R74.1, R75.1, R76.1, R77.1, R78.1, R79.1, R86.1, R87.1, R88.1, R89.1, R90.1, R91.1, R93.1, R94.1, R96.1, R97.1, R99.1, R101.1, SW2.1, U1.13 (GND), U2.4 (GND), U2.5 (A2), U2.6 (A1), U2.7 (A0), U6.8 (PGND), U6.11 (GND), U6.25 (NC), U7.8 (PGND), U7.11 (GND), U7.25 (NC), U8.8 (PGND), U8.11 (GND), U8.25 (NC), U10.47 (VREG_PGND), U10.61 (GND), U11.2, U11.4, U12.4 (GND), U13.4 (GND), U14.4 (GND), U15.11 (GND), U17.7 (GND), U18.7 (GND), U19.3 (GND), U19.11 (GND), U20.3 (GND), U20.11 (GND), U21.3 (GND), U21.11 (GND), U22.3 (GND), U22.11 (GND), U23.3 (GND), U23.11 (GND), U24.3 (GND), U24.11 (GND), U25.3 (A1), U25.4 (A0), U25.13 (GND), U26.3 (A1), U26.13 (GND), U27.3 (A1), U27.13 (GND), U28.4 (A0), U28.13 (GND), U29.13 (GND), U30.13 (GND), U31.3 (GND), U31.11 (GND), U32.3 (GND), U32.11 (GND), U33.13 (GND), U34.4 (A0), U34.13 (GND), U35.4 (GND), U35.5 (A2), U35.6 (A1), U36.4 (GND), U36.5 (A2), U36.7 (A0), USB1.1 (GND), USB1.12 (GND), USB1.13 (SHELL), USB1.14 (SHELL)
GPIO_DRIVE_EN_1: U10.7 (GPIO4), U15.1 (A1)
GPIO_DRIVE_EN_2: U10.8 (GPIO5), U15.3 (A2)
GPIO_DRIVE_EN_3: U10.9 (GPIO6), U15.4 (A3)
GPIO_DRIVE_EN_4: U10.10 (GPIO7), U15.5 (A4)
GPIO_DRIVE_EN_5: U10.12 (GPIO8), U15.6 (A5)
GPIO_DRIVE_EN_6: U10.13 (GPIO9), U15.7 (A6)
GPIO_SCIENCE_EN: U10.15 (GPIO11), U15.9 (A8)
GPIO__ARM_EN: U10.14 (GPIO10), U15.8 (A7)
unnamed: C54.2, R86.2
unnamed: C55.2, R87.2
unnamed: C56.2, R88.2
unnamed: C57.2, R89.2
unnamed: C58.2, R90.2
unnamed: C59.2, R91.2
unnamed: C63.2, R99.2
unnamed: C65.2, R101.2
unnamed: D1.1 (A), R13.2, U3.1 (GND)
unnamed: D2.1 (A), R14.2, U4.1 (GND)
unnamed: D3.1 (A), R15.2, U5.1 (GND)
unnamed: LED1.1 (A), R42.2
unnamed: C54.1, Q1.1 (G), R80.2, U19.6 (TGDN)
unnamed: C55.1, Q2.1 (G), R81.2, U20.6 (TGDN)
unnamed: C56.1, Q3.1 (G), R82.2, U21.6 (TGDN)
unnamed: C57.1, Q4.1 (G), R83.2, U22.6 (TGDN)
unnamed: C58.1, Q5.1 (G), R84.2, U23.6 (TGDN)
unnamed: C59.1, Q6.1 (G), R85.2, U24.6 (TGDN)
unnamed: C63.1, Q7.1 (G), R98.2, U31.6 (TGDN)
unnamed: C65.1, Q8.1 (G), R100.2, U32.6 (TGDN)
unnamed: U1.1 (SH+), U1.2 (IN+)
unnamed: U1.9 (SH–), U1.10 (IN–)
unnamed: R16.1, U3.16 (DIA_EN)
unnamed: R1.2, R2.1, U3.4 (EN)
unnamed: R10.1, U3.3 (LATCH)
unnamed: R17.1, U3.14 (SEL1)
unnamed: R7.1, U3.2 (SNS)
unnamed: R18.1, U4.16 (DIA_EN)
unnamed: R3.2, R4.1, U4.4 (EN)
unnamed: R11.1, U4.3 (LATCH)
unnamed: R19.1, U4.14 (SEL1)
unnamed: R8.1, U4.2 (SNS)
unnamed: C5.1, R24.2, TP5.1 (1_1), U4.6 (VOUT), U7.5 (VIN)
unnamed: R20.1, U5.16 (DIA_EN)
unnamed: R5.2, R6.1, U5.4 (EN)
unnamed: R12.1, U5.3 (LATCH)
unnamed: R21.1, U5.14 (SEL1)
unnamed: R9.1, U5.2 (SNS)
unnamed: C6.1, R26.2, TP6.1 (1_1), U5.6 (VOUT), U8.5 (VIN)
unnamed: C13.1, U6.20 (BST)
unnamed: R22.1, R23.2, U6.4 (EN/UV)
unnamed: C16.2, R31.1, R33.2, U6.24 (FB)
unnamed: C10.1, U6.21 (INTVCC)
unnamed: R28.2, U6.3 (RT)
unnamed: C13.2, SW1.1, U6.15 (SW)
unnamed: C7.1, U6.2 (TR/SS)
unnamed: C14.1, U7.20 (BST)
unnamed: R24.1, R25.2, U7.4 (EN/UV)
unnamed: C17.2, R32.1, R35.2, U7.24 (FB)
unnamed: C11.1, U7.21 (INTVCC)
unnamed: R29.2, U7.3 (RT)
unnamed: C14.2, L1.1, U7.15 (SW)
unnamed: C8.1, U7.2 (TR/SS)
unnamed: C15.1, U8.20 (BST)
unnamed: R26.1, R27.2, U8.4 (EN/UV)
unnamed: C18.2, R34.1, R36.2, U8.24 (FB)
unnamed: C12.1, U8.21 (INTVCC)
unnamed: R30.2, U8.3 (RT)
unnamed: C15.2, U8.15 (SW), U9.1
unnamed: C9.1, U8.2 (TR/SS)
unnamed: C28.1, R38.2, U10.46 (VREG_AVDD)
unnamed: R51.1, U13.1 (EN)
unnamed: R59.1, U13.5 (READY)
unnamed: R52.1, U14.1 (EN)
unnamed: R60.1, U14.5 (READY)
unnamed: C48.1, U19.9 (BST)
unnamed: R62.1, R63.2, U19.5 (OVLO)
unnamed: R80.1, U19.7 (TGUP)
unnamed: C48.2, D4.2, U19.8 (TS)
unnamed: R74.2, U19.2 (VCCUV)
unnamed: C49.1, U20.9 (BST)
unnamed: R64.1, R65.2, U20.5 (OVLO)
unnamed: R81.1, U20.7 (TGUP)
unnamed: C49.2, D5.2, U20.8 (TS)
unnamed: R75.2, U20.2 (VCCUV)
unnamed: C50.1, U21.9 (BST)
unnamed: R66.1, R67.2, U21.5 (OVLO)
unnamed: R82.1, U21.7 (TGUP)
unnamed: C50.2, D6.2, U21.8 (TS)
unnamed: R76.2, U21.2 (VCCUV)
unnamed: C51.1, U22.9 (BST)
unnamed: R68.1, R69.2, U22.5 (OVLO)
unnamed: R83.1, U22.7 (TGUP)
unnamed: C51.2, D7.2, U22.8 (TS)
unnamed: R77.2, U22.2 (VCCUV)
unnamed: C52.1, U23.9 (BST)
unnamed: R70.1, R71.2, U23.5 (OVLO)
unnamed: R84.1, U23.7 (TGUP)
unnamed: C52.2, D8.2, U23.8 (TS)
unnamed: R78.2, U23.2 (VCCUV)
unnamed: C53.1, U24.9 (BST)
unnamed: R72.1, R73.2, U24.5 (OVLO)
unnamed: R85.1, U24.7 (TGUP)
unnamed: C53.2, D9.2, U24.8 (TS)
unnamed: R79.2, U24.2 (VCCUV)
unnamed: U25.1 (SH+), U25.2 (IN+)
unnamed: U25.9 (SH–), U25.10 (IN–)
unnamed: U26.1 (SH+), U26.2 (IN+)
unnamed: U26.9 (SH–), U26.10 (IN–)
unnamed: U27.1 (SH+), U27.2 (IN+)
unnamed: U27.9 (SH–), U27.10 (IN–)
unnamed: U28.1 (SH+), U28.2 (IN+)
unnamed: U28.9 (SH–), U28.10 (IN–)
unnamed: U29.1 (SH+), U29.2 (IN+)
unnamed: U29.9 (SH–), U29.10 (IN–)
unnamed: U30.1 (SH+), U30.2 (IN+)
unnamed: U30.9 (SH–), U30.10 (IN–)
unnamed: C62.1, U31.9 (BST)
unnamed: R92.1, R93.2, U31.5 (OVLO)
unnamed: R98.1, U31.7 (TGUP)
unnamed: C62.2, D10.2, U31.8 (TS)
unnamed: R94.2, U31.2 (VCCUV)
unnamed: C64.1, U32.9 (BST)
unnamed: R95.1, R96.2, U32.5 (OVLO)
unnamed: R100.1, U32.7 (TGUP)
unnamed: C64.2, D11.2, U32.8 (TS)
unnamed: R97.2, U32.2 (VCCUV)
unnamed: U33.1 (SH+), U33.2 (IN+)
unnamed: U33.9 (SH–), U33.10 (IN–)
unnamed: U34.1 (SH+), U34.2 (IN+)
unnamed: U34.9 (SH–), U34.10 (IN–)
unnamed: R57.1, USB1.4 (CC1)
unnamed: R58.1, USB1.10 (CC2)
PI_SCL_0: R49.1, U10.3 (GPIO1), U13.3 (SCLIN)
PI_SCL_1: R50.1, U10.5 (GPIO3), U14.3 (SCLIN)
PI_SDA_0: R47.1, U10.2 (GPIO0), U13.6 (SDAIN)
PI_SDA_1: R48.1, U10.4 (GPIO2), U14.6 (SDAIN)
USB_D+: R40.2, USB1.6 (DP1), USB1.8 (DP2)
USB_D-: R41.2, USB1.5 (DN2), USB1.7 (DN1)
VBUS_USB: USB1.2 (VBUS), USB1.11 (VBUS)
